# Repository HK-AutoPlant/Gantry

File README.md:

# Gantry

## Prerequisites
* python 3.8 or lower, pyqt5-tools will not install for python 3.9
* pip install pyqt5
* pip install pyqt5-tools
* pip install pyqtgraph
* pip install odrive
* pip install paho-mqtt

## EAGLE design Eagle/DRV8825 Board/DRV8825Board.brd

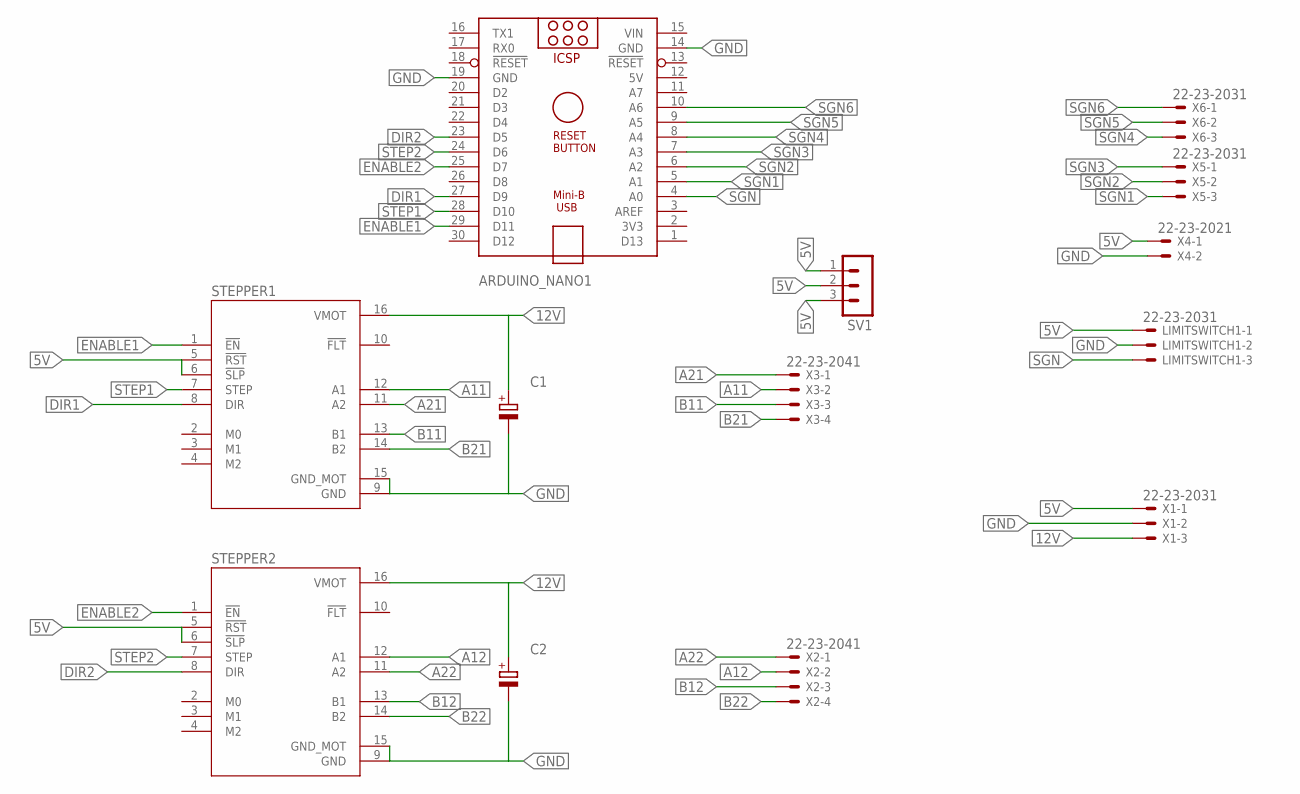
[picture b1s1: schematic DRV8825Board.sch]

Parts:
ARDUINO_NANO1: ARDUINO_NANO
C1, C2: CPOL-EUE2.5-6; E2,5-6
LIMITSWITCH1: 22-23-2031
STEPPER1, STEPPER2: DRV8825_STEPPER_MOTOR_DRIVER_CARRIER; IC_DRV8825_STEPPER_MOTOR_DRIVER_CARRIER
SV1: MA03-1
X1, X5, X6: 22-23-2031
X2, X3: 22-23-2041
X4: 22-23-2021

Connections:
5V: ARDUINO_NANO1.12 (5V), LIMITSWITCH1.1, STEPPER1.5 (!RST), STEPPER1.6 (!SLP), STEPPER2.5 (!RST), STEPPER2.6 (!SLP), SV1.1, SV1.2, SV1.3, X1.1, X4.1
12V: C1.+, C2.+, STEPPER1.16 (VMOT), STEPPER2.16 (VMOT), X1.3
A11: STEPPER1.12 (A1), X3.2
A12: STEPPER2.12 (A1), X2.2
A21: STEPPER1.11 (A2), X3.1
A22: STEPPER2.11 (A2), X2.1
B11: STEPPER1.13 (B1), X3.3
B12: STEPPER2.13 (B1), X2.3
B21: STEPPER1.14 (B2), X3.4
B22: STEPPER2.14 (B2), X2.4
DIR1: ARDUINO_NANO1.27 (D9), STEPPER1.8 (DIR)
DIR2: ARDUINO_NANO1.23 (D5), STEPPER2.8 (DIR)
ENABLE1: ARDUINO_NANO1.29 (D11), STEPPER1.1 (!EN)
ENABLE2: ARDUINO_NANO1.25 (D7), STEPPER2.1 (!EN)
GND: ARDUINO_NANO1.14 (GND), ARDUINO_NANO1.19 (GND), C1.-, C2.-, LIMITSWITCH1.2, STEPPER1.9 (GND), STEPPER1.15 (GND_MOT), STEPPER2.9 (GND), STEPPER2.15 (GND_MOT), X1.2, X4.2
SGN: ARDUINO_NANO1.4 (A0), LIMITSWITCH1.3
SGN1: ARDUINO_NANO1.5 (A1), X5.3
SGN2: ARDUINO_NANO1.6 (A2), X5.2
SGN3: ARDUINO_NANO1.7 (A3), X5.1
SGN4: ARDUINO_NANO1.8 (A4), X6.3
SGN5: ARDUINO_NANO1.9 (A5), X6.2
SGN6: ARDUINO_NANO1.10 (A6), X6.1
STEP1: ARDUINO_NANO1.28 (D10), STEPPER1.7 (STEP)
STEP2: ARDUINO_NANO1.24 (D6), STEPPER2.7 (STEP)
VIN: ARDUINO_NANO1.15 (VIN)

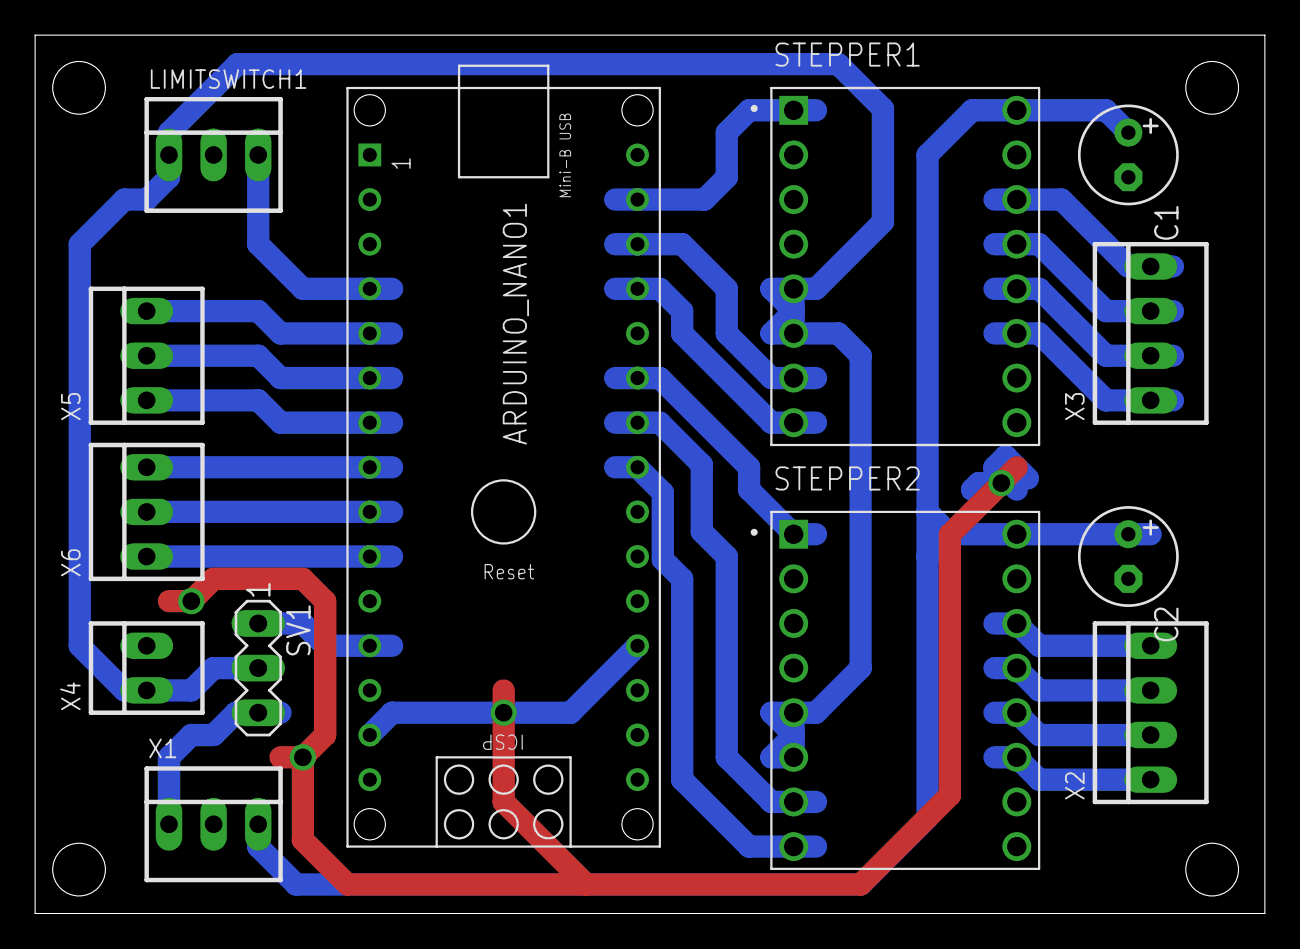
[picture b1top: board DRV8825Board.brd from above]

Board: 2 copper layers, 70.0 x 50.0 mm, 13 parts (0 on the bottom side), 24 nets.

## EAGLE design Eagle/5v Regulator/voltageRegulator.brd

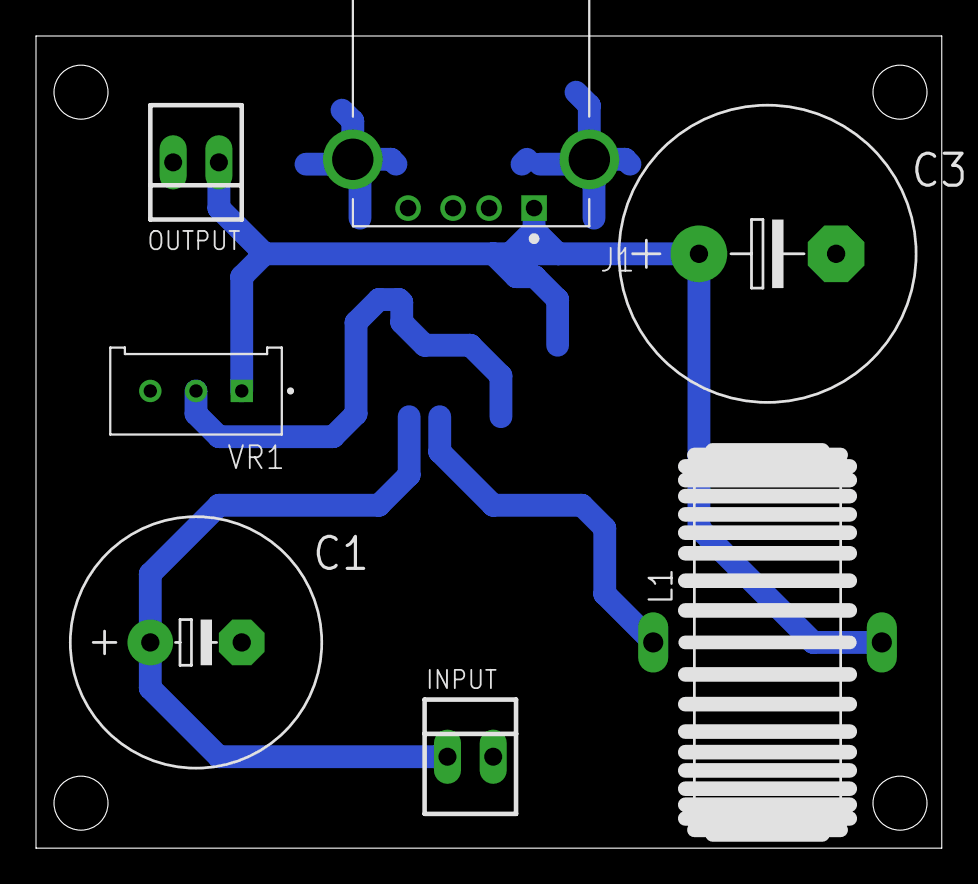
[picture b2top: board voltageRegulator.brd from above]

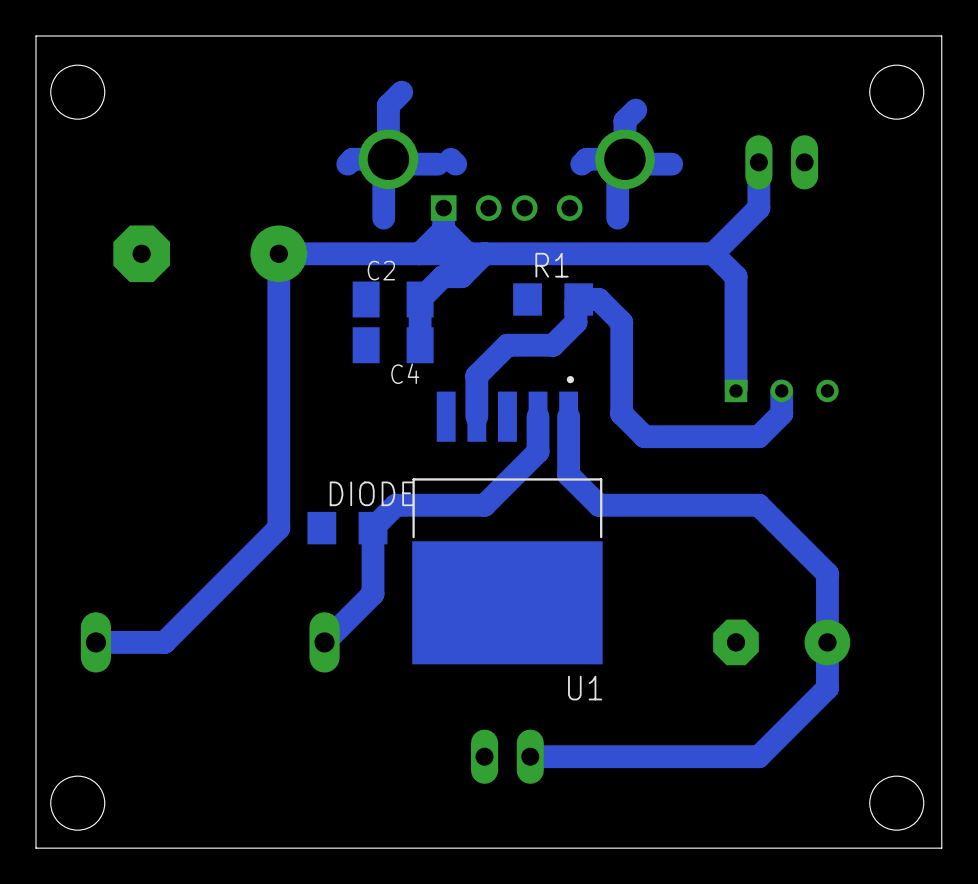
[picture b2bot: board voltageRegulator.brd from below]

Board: 2 copper layers, 50.3 x 45.1 mm, 12 parts (5 on the bottom side), 5 nets.

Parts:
C1: 100 uF; E5-13
C2, C4: C1206K
C3: 1000 uF; E7,5-16
DIODE: 3000; R1206
INPUT: 22-23-2021
J1: 292303-1; TE_292303-1
L1: SFT1030
OUTPUT: 22-23-2021
R1: 1000; R1206
U1: LM2576HVS-5.0/NOPB; DDPAK/TO-263-5
VR1: 3296W-1-250; TRIM_3296W-1-250

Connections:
FEEDBACK: R1.2, U1.4, VR1.2
GND: C1.-, C2.1, C3.-, C4.2, DIODE.1, INPUT.2, J1.4, J1.SH1, J1.SH2, OUTPUT.2, R1.1, U1.3, U1.5, U1.6, VR1.3
LOAD+: C2.2, C3.+, C4.1, J1.1, L1.2, OUTPUT.1, VR1.1
OUTPUT: DIODE.2, L1.1, U1.2
VCC: C1.+, INPUT.1, U1.1

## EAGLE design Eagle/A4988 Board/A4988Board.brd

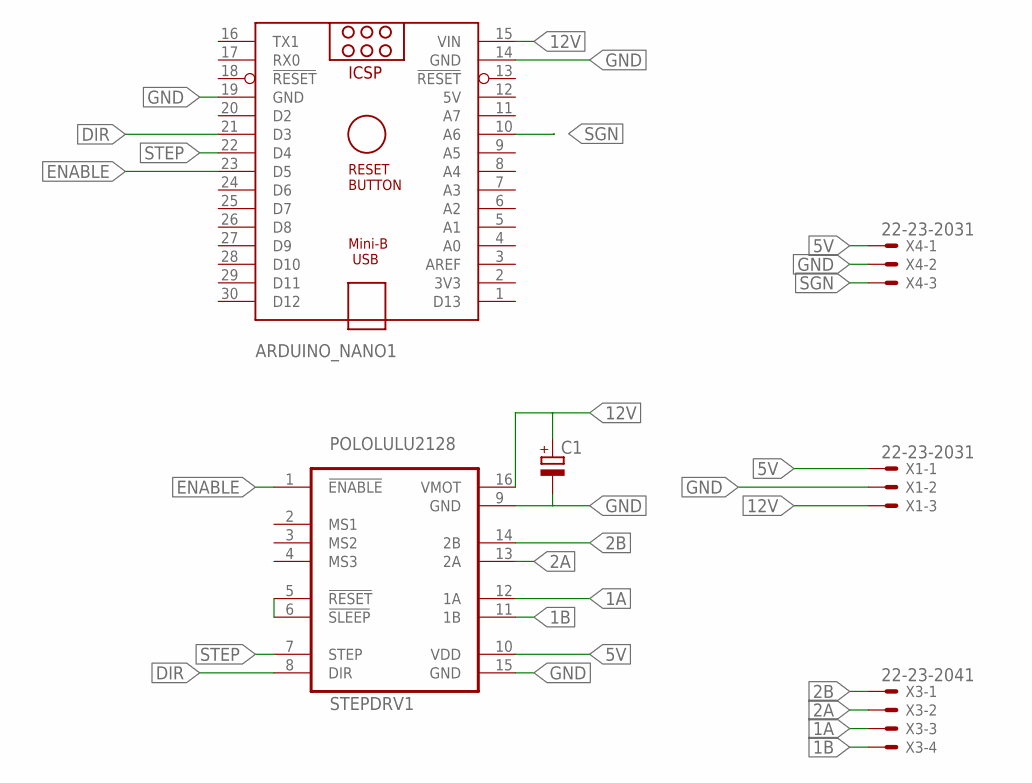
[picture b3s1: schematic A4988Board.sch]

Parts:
ARDUINO_NANO1: ARDUINO_NANO
C1: CPOL-EUE2.5-6; E2,5-6
STEPDRV1: POLOLULU2128
X1, X4: 22-23-2031
X3: 22-23-2041

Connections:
1A: STEPDRV1.12 (1A), X3.3
1B: STEPDRV1.11 (1B), X3.4
2A: STEPDRV1.13 (2A), X3.2
2B: STEPDRV1.14 (2B), X3.1
5V: ARDUINO_NANO1.12 (5V), STEPDRV1.10 (VDD), X1.1, X4.1
12V: ARDUINO_NANO1.15 (VIN), C1.+, STEPDRV1.16 (VMOT), X1.3
DIR: ARDUINO_NANO1.21 (D3), STEPDRV1.8 (DIR)
ENABLE: ARDUINO_NANO1.23 (D5), STEPDRV1.1 (!ENABLE)
GND: ARDUINO_NANO1.14 (GND), ARDUINO_NANO1.19 (GND), C1.-, STEPDRV1.9 (GND), STEPDRV1.15 (GND), X1.2, X4.2
unnamed: STEPDRV1.5 (!RESET), STEPDRV1.6 (!SLEEP)
SGN: ARDUINO_NANO1.10 (A6), X4.3
STEP: ARDUINO_NANO1.22 (D4), STEPDRV1.7 (STEP)

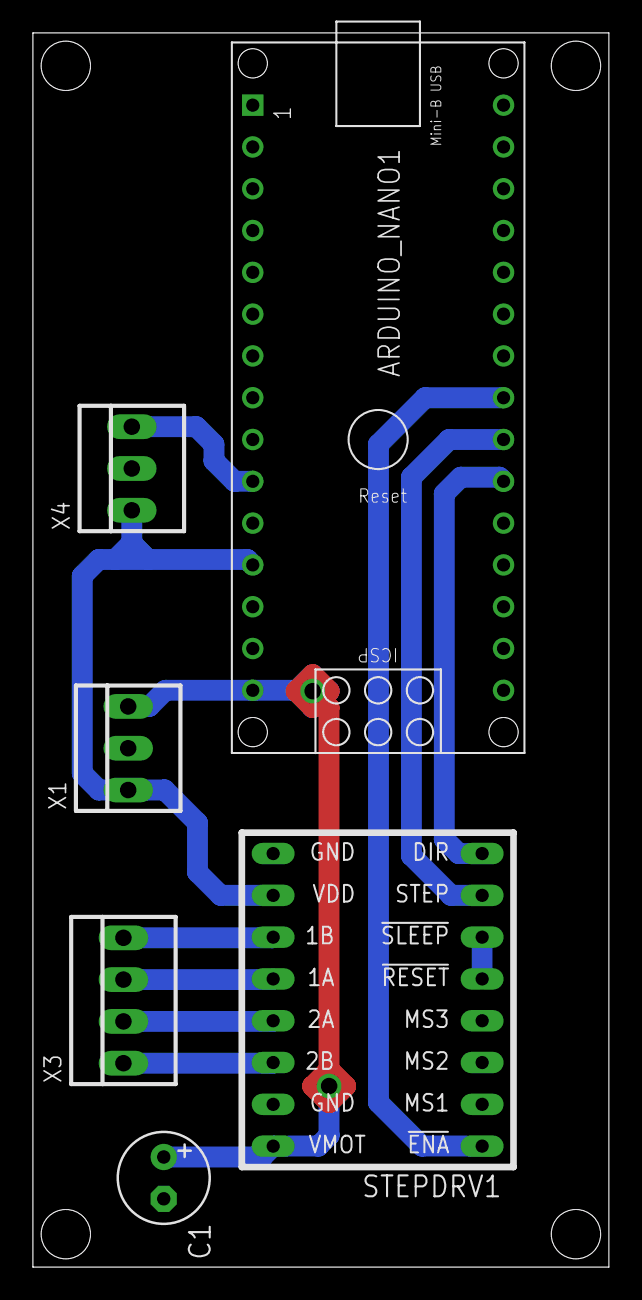
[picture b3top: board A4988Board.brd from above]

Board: 2 copper layers, 35.0 x 75.0 mm, 6 parts (0 on the bottom side), 12 nets.

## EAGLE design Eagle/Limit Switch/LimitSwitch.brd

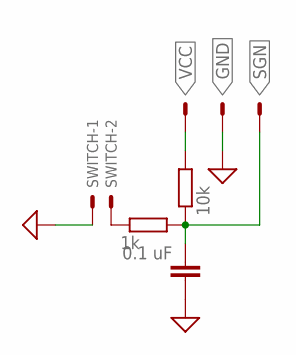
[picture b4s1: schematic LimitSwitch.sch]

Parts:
C1: 0.1 uF; C1206
INPUT: 22-23-2031
R3: 10k; R1206
R4: 1k; R1206
SWITCH: 22-23-2021

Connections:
GND: C1.2, INPUT.2, SWITCH.1
unnamed: R4.1, SWITCH.2
SGN: C1.1, INPUT.3, R3.1, R4.2
VCC: INPUT.1, R3.2

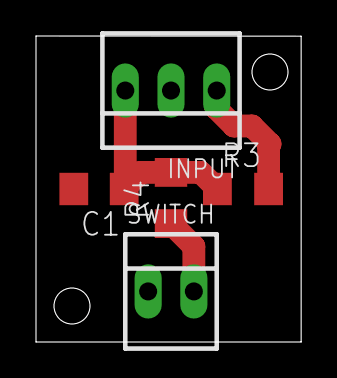
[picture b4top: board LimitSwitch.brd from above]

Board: 2 copper layers, 14.7 x 17.0 mm, 5 parts (0 on the bottom side), 4 nets.

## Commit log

2020-09-18 Initial push
2020-09-18 updaterad layout
2020-09-18 rensat kommentarer
2020-09-21 Added code for the zAxis
2020-09-22 Added calculations for the passive components
2020-09-22 Removed the calculations and added the eagle files
2020-09-22 removed 5v reg
2020-09-22 Added C++ Code
2020-09-23 updated the A4988 board with an Arduino
2020-09-23 updated the regulator board
2020-09-24 test
2020-09-25 vesrion2
2020-09-26 "version3"
2020-09-26 movement and abttery estimation
2020-09-26 buffer zone chaning color
2020-09-27 inte mycket nytt
2020-09-27 Tabs
2020-09-28 la till iconinterface
2020-09-28 nya iconer
2020-09-28 Added zAxis control board with DRV8825 driver
2020-09-28 tab added to script
2020-09-28 åka med pilar
2020-09-28 added Måns gui
2020-09-29 Added a fan controller circuit
2020-09-30 flytta till träd position
2020-09-30 plottar
2020-09-30 Snyggat till koden med indelade sektioner och tagit bort gammalt
2020-10-06 updated classes
2020-10-07 utan url
2020-10-07 utan kamera
2020-10-08 försöker fixa grids v1
2020-10-08 auto res
2020-10-08 auto res v2
2020-10-09 random
2020-10-09 xbox controller v1
2020-10-09 added auto
2020-10-09 Auto stash before rebase of "origin/master"
    auto v2
2020-10-09 Updated the zAxis drivers and the python script that communicates via USB
2020-10-09 updated auto
2020-10-26 Updated the voltage regulator board
2020-10-28 Auto sequence progress. zAxis implemented
2020-10-29 bild bara
2020-10-29 mindre
2020-10-30 printing
2020-11-02 Added Prerequisites
2020-11-02 small update
2020-11-02 endstops
2020-11-04 not much
2020-11-05 cleaning
2020-11-11 Updated the voltage regulator schematic
2020-11-11 updated comments on the python communication script
2020-11-11 från philip
2020-11-11 Updated some functions
2020-11-11 Auto stash before rebase of "origin/master"
    further zaxis work
2020-11-11 spelling
2020-11-13 Added a script that recognizes the port of an Arduino
2020-11-13 Auto stash before rebase of "origin/master"
2020-11-16 Added a return message function
2020-11-18 minor changes
2020-11-18 Added automatic detection of USB port
2020-11-18 fixed serial number
2020-11-24 Corrected some obvious errors
2020-11-24 Banned .DS_Store
2020-11-24 lite auto
2020-11-25 Added new function to read all limitswitces
2020-11-25 Updated to include all the limitswitches from the gripper
2020-11-25 Added a safety functionality that does not let the motor run until it has been homed
2020-11-25 Added function to move to a specific position
2020-11-25 added gripper to gui
2020-11-25 Updated functions
2020-11-25 Updated so that the code returns a status update
2020-11-25 Auto stash before rebase of "origin/master"
    small
2020-11-26 fixing merge issue......
2020-11-29 File for those who use Arduino IDE
2020-11-30 Added PlatformIO folder
2020-11-30 added CCx and CCY separately in treehive
2020-12-01 xbox added
2020-12-01 minor
2020-12-02 Added simscape model
2020-12-03 Updated some custom functions
2020-12-07 last
2020-12-12 sim last added
